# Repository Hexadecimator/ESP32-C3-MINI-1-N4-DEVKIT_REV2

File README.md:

# ESP32-C3-MINI-1-N4-DEVKIT_REV2
New and improved ESP32-C3-MINI-1-N4 Devkit

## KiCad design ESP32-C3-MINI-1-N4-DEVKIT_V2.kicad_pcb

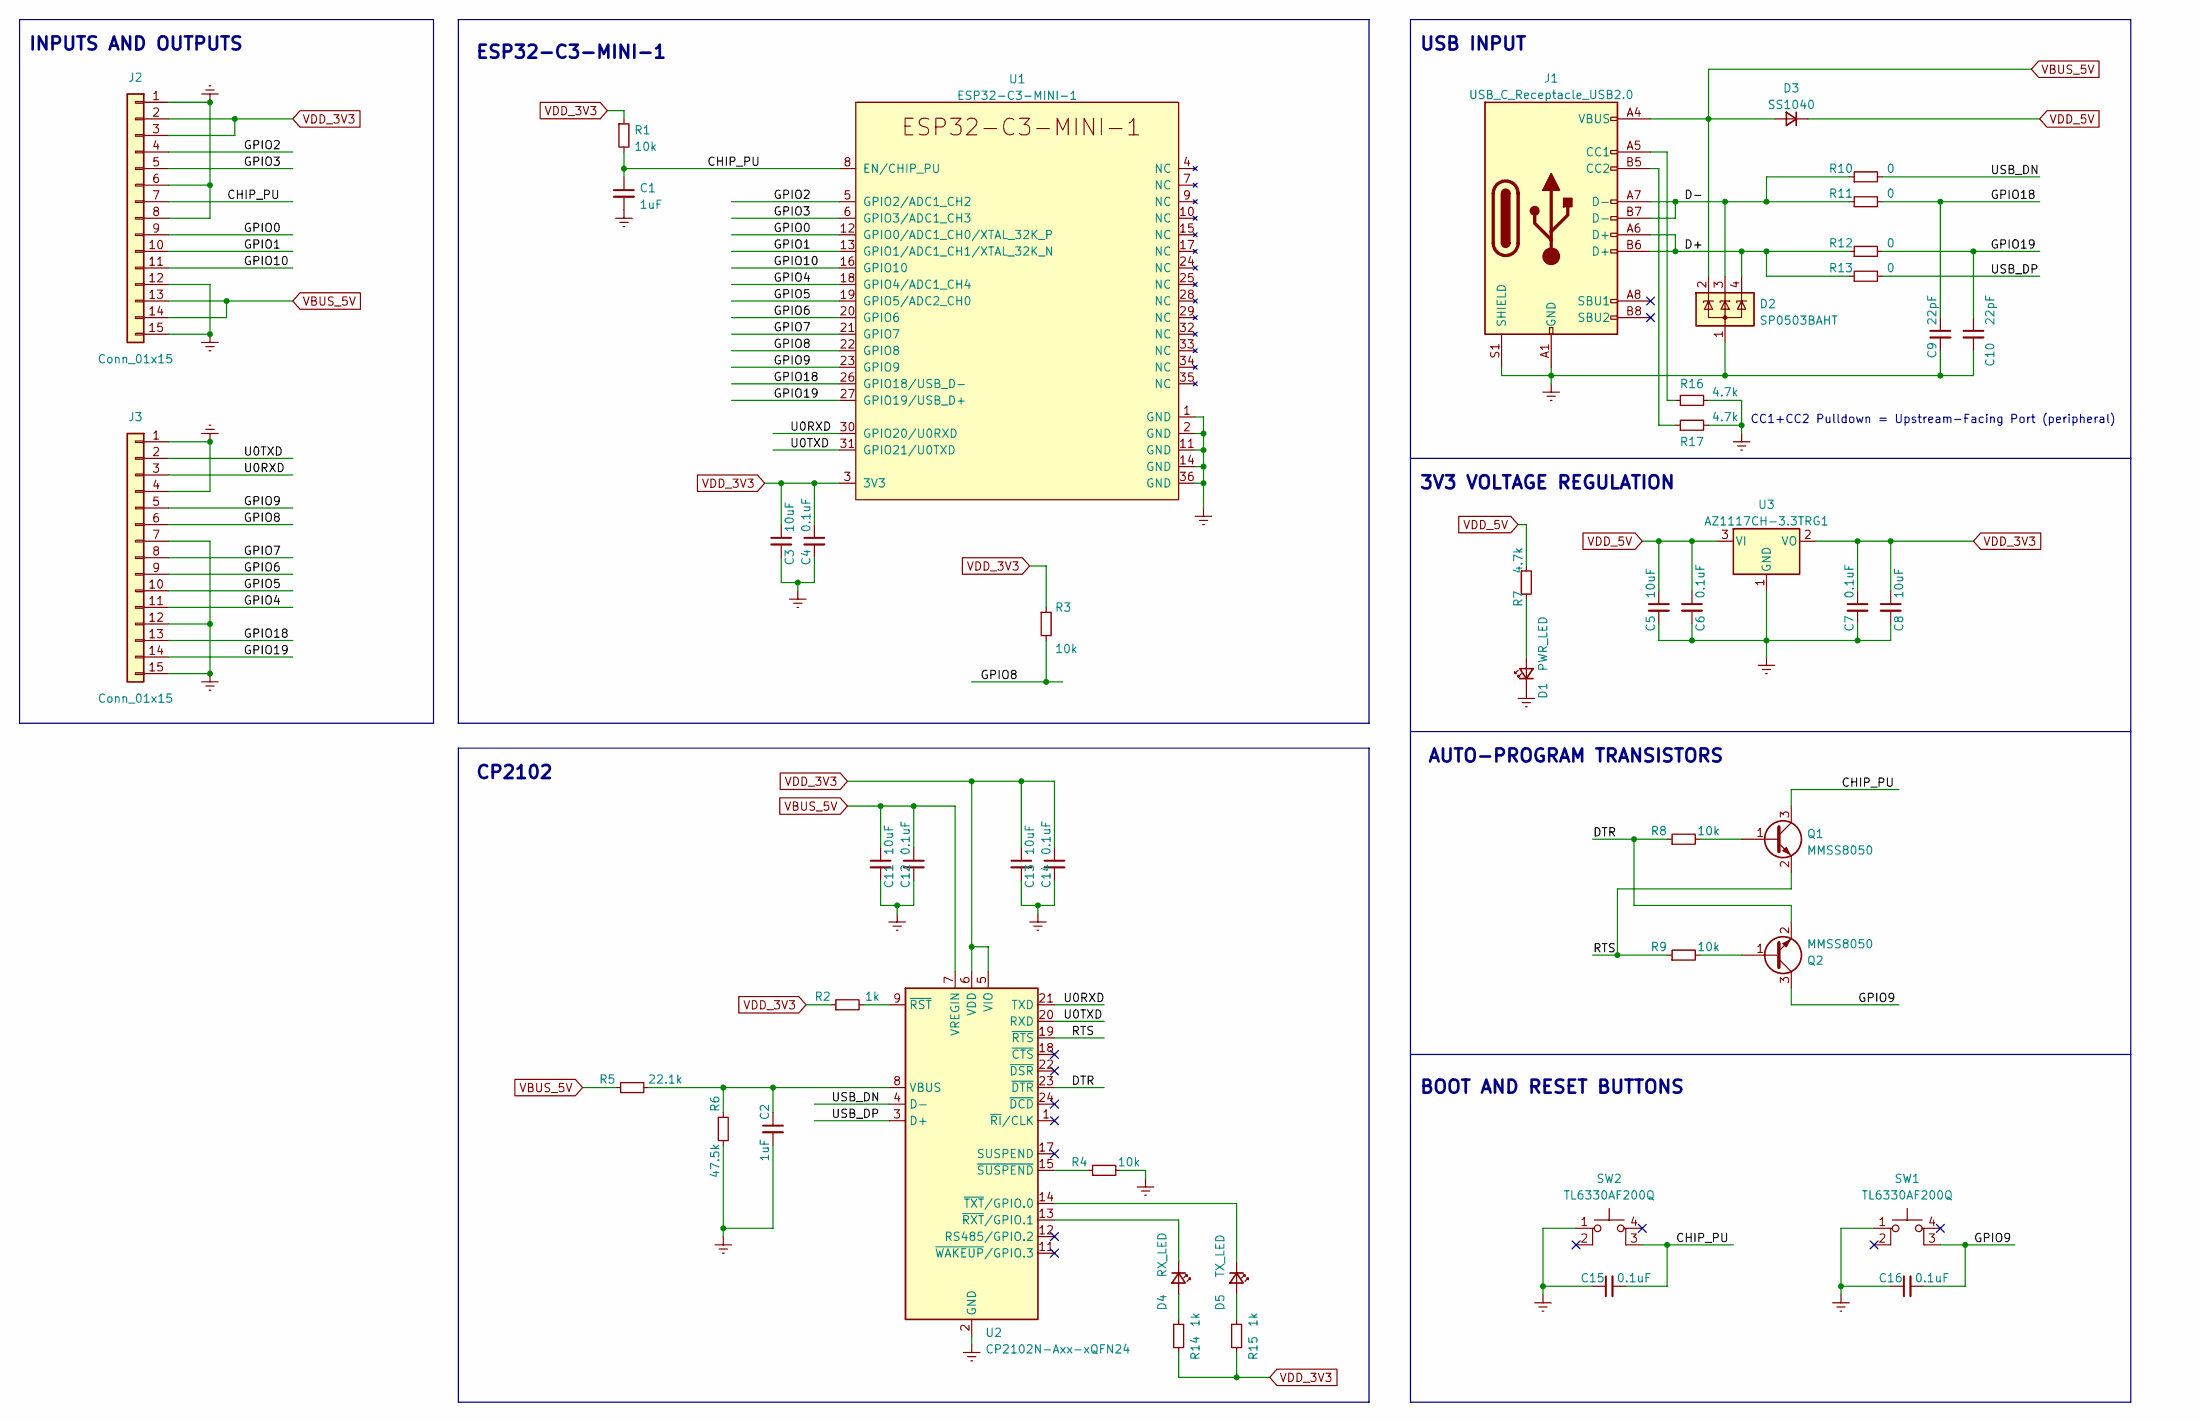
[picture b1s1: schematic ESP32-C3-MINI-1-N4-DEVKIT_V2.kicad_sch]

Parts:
C1, C2: 1uF; C_0603_1608Metric
C3, C5, C8, C11, C13: 10uF; C_0805_2012Metric
C4, C6, C7, C12, C14, C15, C16: 0.1uF; C_0603_1608Metric
C9, C10: 22pF; C_0603_1608Metric
D1: PWR_LED; D_0603_1608Metric
D2: SP0503BAHT; SOT-143
D3: SS1040; D_SOD-123
D4: RX_LED; D_0603_1608Metric
D5: TX_LED; D_0603_1608Metric
J1: USB_C_Receptacle_USB2.0; USB_C_Receptacle_HRO_TYPE-C-31-M-12
J2, J3: Conn_01x15; PinHeader_1x15_P2.54mm_Vertical
Q1, Q2: MMSS8050; SOT-23
R1, R3, R4, R8, R9: 10k; R_0603_1608Metric
R2, R14, R15: 1k; R_0603_1608Metric
R5: 22.1k; R_0603_1608Metric
R6: 47.5k; R_0603_1608Metric
R7, R16, R17: 4.7k; R_0603_1608Metric
R10, R11, R12, R13: 0; R_0603_1608Metric
SW1, SW2: TL6330AF200Q; SW_Push_1P1T_NO_CK_KMR2
U1: ESP32-C3-MINI-1
U2: CP2102N-Axx-xQFN24; QFN-24-1EP_4x4mm_P0.5mm_EP2.6x2.6mm
U3: AZ1117CH-3.3TRG1; SOT-223-3_TabPin2

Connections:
/CHIP_PU: C1.1, C15.2, J2.7, Q1.3 (C), R1.2, SW2.3 (K), U1.8 (EN/CHIP_PU)
/D+: D2.4 (K), J1.A6 (D+), J1.B6 (D+), R12.1, R13.1
/D-: D2.3 (K), J1.A7 (D-), J1.B7 (D-), R10.1, R11.1
/DTR: Q2.2 (E), R8.1, U2.23 (~DTR)
/GPIO0: J2.9, U1.12 (GPIO0/ADC1_CH0/XTAL_32K_P)
/GPIO1: J2.10, U1.13 (GPIO1/ADC1_CH1/XTAL_32K_N)
/GPIO2: J2.4, U1.5 (GPIO2/ADC1_CH2)
/GPIO3: J2.5, U1.6 (GPIO3/ADC1_CH3)
/GPIO4: J3.11, U1.18 (GPIO4/ADC1_CH4)
/GPIO5: J3.10, U1.19 (GPIO5/ADC2_CH0)
/GPIO6: J3.9, U1.20 (GPIO6)
/GPIO7: J3.8, U1.21 (GPIO7)
/GPIO8: J3.6, R3.2, U1.22 (GPIO8)
/GPIO9: C16.2, J3.5, Q2.3 (C), SW1.3 (K), U1.23 (GPIO9)
/GPIO10: J2.11, U1.16 (GPIO10)
/GPIO18: C9.1, J3.13, R11.2, U1.26 (GPIO18/USB_D-)
/GPIO19: C10.1, J3.14, R12.2, U1.27 (GPIO19/USB_D+)
/RTS: Q1.2 (E), R9.1, U2.19 (~RTS)
/U0RXD: J3.3, U1.30 (GPIO20/U0RXD), U2.21 (TXD)
/U0TXD: J3.2, U1.31 (GPIO21/U0TXD), U2.20 (RXD)
/USB_DN: R10.2, U2.4 (D-)
/USB_DP: R13.2, U2.3 (D+)
Earth: C1.2, C2.2, C3.2, C4.2, C5.2, C6.2, C7.2, C8.2, C9.2, C10.2, C11.2, C12.2, C13.2, C14.2, C15.1, C16.1, D1.1 (K), D2.1 (A), J1.A1 (GND), J1.A12 (GND), J1.B1 (GND), J1.B12 (GND), J1.S1 (SHIELD), J2.1, J2.6, J2.8, J2.12, J2.15, J3.1, J3.4, J3.7, J3.12, J3.15, R4.2, R6.2, R16.2, R17.2, SW1.1, SW2.1, U1.1 (GND), U1.2 (GND), U1.11 (GND), U1.14 (GND), U1.36 (GND), U2.2 (GND), U2.25 (GND), U3.1 (GND)
unnamed: D1.2 (A), R7.2
unnamed: D4.1 (K), U2.13 (~RXT/GPIO.1)
unnamed: D4.2 (A), R14.1
unnamed: D5.1 (K), U2.14 (~TXT/GPIO.0)
unnamed: D5.2 (A), R15.1
unnamed: J1.A5 (CC1), R16.1
unnamed: J1.B5 (CC2), R17.1
unnamed: Q1.1 (B), R8.2
unnamed: Q2.1 (B), R9.2
unnamed: R2.2, U2.9 (~RST)
unnamed: R4.1, U2.15 (~SUSPEND)
unnamed: C2.1, R5.2, R6.1, U2.8 (VBUS)
VBUS_5V: C11.1, C12.1, D2.2 (K), D3.2 (A), J1.A4 (VBUS), J1.A9 (VBUS), J1.B4 (VBUS), J1.B9 (VBUS), J2.13, J2.14, R5.1, U2.7 (VREGIN)
VDD_3V3: C3.1, C4.1, C7.1, C8.1, C13.1, C14.1, J2.2, J2.3, R1.1, R2.1, R3.1, R14.2, R15.2, U1.3 (3V3), U2.5 (VIO), U2.6 (VDD), U3.2 (VO)
VDD_5V: C5.1, C6.1, D3.1 (K), R7.1, U3.3 (VI)

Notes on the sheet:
ESP32-C3-MINI-1
3V3 VOLTAGE REGULATION
CC1+CC2 Pulldown = Upstream-Facing Port (peripheral)
USB INPUT
AUTO-PROGRAM TRANSISTORS
INPUTS AND OUTPUTS
CP2102
BOOT AND RESET BUTTONS

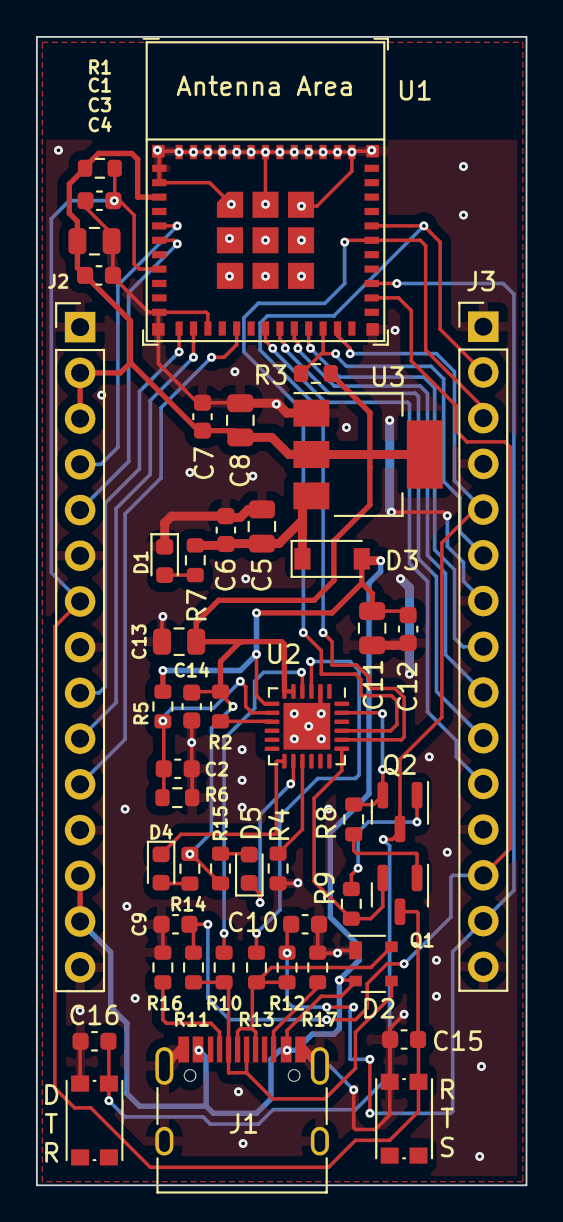
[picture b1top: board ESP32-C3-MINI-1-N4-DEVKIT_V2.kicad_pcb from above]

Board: 2 copper layers, 27.2 x 63.8 mm, 48 parts (0 on the bottom side), 38 nets.

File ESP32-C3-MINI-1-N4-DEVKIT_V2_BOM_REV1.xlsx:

Source:
Date: | 44788.761562500003
Tool: | Eeschema (6.0.5)
Generator:
Component Count: | 48
Individual Components:
Reference(s) | Value | LibPart | Footprint | Datasheet
C1 | 1uF | Device:C_Small | Capacitor_SMD:C_0603_1608Metric | ~
C2 | 1uF | Device:C_Small | Capacitor_SMD:C_0603_1608Metric | ~
C3 | 10uF | Device:C_Small | Capacitor_SMD:C_0805_2012Metric | ~
C4 | 0.1uF | Device:C_Small | Capacitor_SMD:C_0603_1608Metric | ~
C5 | 10uF | Device:C_Small | Capacitor_SMD:C_0805_2012Metric | ~
C6 | 0.1uF | Device:C_Small | Capacitor_SMD:C_0603_1608Metric | ~
C7 | 0.1uF | Device:C_Small | Capacitor_SMD:C_0603_1608Metric | ~
C8 | 10uF | Device:C_Small | Capacitor_SMD:C_0805_2012Metric | ~
C9 | 22pF | Device:C_Small | Capacitor_SMD:C_0603_1608Metric | ~
C10 | 22pF | Device:C_Small | Capacitor_SMD:C_0603_1608Metric | ~
C11 | 10uF | Device:C_Small | Capacitor_SMD:C_0805_2012Metric | ~
C12 | 0.1uF | Device:C_Small | Capacitor_SMD:C_0603_1608Metric | ~
C13 | 10uF | Device:C_Small | Capacitor_SMD:C_0805_2012Metric | ~
C14 | 0.1uF | Device:C_Small | Capacitor_SMD:C_0603_1608Metric | ~
C15 | 0.1uF | Device:C_Small | Capacitor_SMD:C_0603_1608Metric | ~
C16 | 0.1uF | Device:C_Small | Capacitor_SMD:C_0603_1608Metric | ~
D1 | PWR_LED | Device:LED_Small | Diode_SMD:D_0603_1608Metric | ~
D2 | SP0503BAHT | Power_Protection:SP0503BAHT | Package_TO_SOT_SMD:SOT-143 | http://www.littelfuse.com/~/media/files/littelfuse/technical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
D3 | SS1040 | Device:D_Small | Diode_SMD:D_SOD-123 | ~
D4 | RX_LED | Device:LED_Small | Diode_SMD:D_0603_1608Metric | ~
D5 | TX_LED | Device:LED_Small | Diode_SMD:D_0603_1608Metric | ~
J1 | USB_C_Receptacle_USB2.0 | Connector:USB_C_Receptacle_USB2.0 | Connector_USB:USB_C_Receptacle_HRO_TYPE-C-31-M-12 | https://www.usb.org/sites/default/files/documents/usb_type-c.zip
J2 | Conn_01x15 | Connector_Generic:Conn_01x15 | Connector_PinHeader_2.54mm:PinHeader_1x15_P2.54mm_Vertical | ~
J3 | Conn_01x15 | Connector_Generic:Conn_01x15 | Connector_PinHeader_2.54mm:PinHeader_1x15_P2.54mm_Vertical | ~
Q1 | MMSS8050 | Device:Q_NPN_BEC | Package_TO_SOT_SMD:SOT-23 | ~
Q2 | MMSS8050 | Device:Q_NPN_BEC | Package_TO_SOT_SMD:SOT-23 | ~
R1 | 10k | Device:R_Small | Resistor_SMD:R_0603_1608Metric | ~
R2 | 1k | Device:R_Small | Resistor_SMD:R_0603_1608Metric | ~
R3 | 10k | Device:R_Small | Resistor_SMD:R_0603_1608Metric | ~
R4 | 10k | Device:R_Small | Resistor_SMD:R_0603_1608Metric | ~
R5 | 22.1k | Device:R_Small | Resistor_SMD:R_0603_1608Metric | ~
R6 | 47.5k | Device:R_Small | Resistor_SMD:R_0603_1608Metric | ~
R7 | 4.7k | Device:R_Small | Resistor_SMD:R_0603_1608Metric | ~
R8 | 10k | Device:R_Small | Resistor_SMD:R_0603_1608Metric | ~
R9 | 10k | Device:R_Small | Resistor_SMD:R_0603_1608Metric | ~
R10 | 0 | Device:R_Small | Resistor_SMD:R_0603_1608Metric | ~
R11 | 0 | Device:R_Small | Resistor_SMD:R_0603_1608Metric | ~
R12 | 0 | Device:R_Small | Resistor_SMD:R_0603_1608Metric | ~
R13 | 0 | Device:R_Small | Resistor_SMD:R_0603_1608Metric | ~
R14 | 1k | Device:R_Small | Resistor_SMD:R_0603_1608Metric | ~
R15 | 1k | Device:R_Small | Resistor_SMD:R_0603_1608Metric | ~
R16 | 4.7k | Device:R_Small | Resistor_SMD:R_0603_1608Metric | ~
R17 | 4.7k | Device:R_Small | Resistor_SMD:R_0603_1608Metric | ~
SW1 | TL6330AF200Q | Switch:SW_MEC_5E | Button_Switch_SMD:SW_Push_1P1T_NO_CK_KMR2 | http://www.apem.com/int/index.php?controller=attachment&id_a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
SW2 | TL6330AF200Q | Switch:SW_MEC_5E | Button_Switch_SMD:SW_Push_1P1T_NO_CK_KMR2 | http://www.apem.com/int/index.php?controller=attachment&id_a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
U1 | ESP32-C3-MINI-1 | Espressif:ESP32-C3-MINI-1 | Espressif:ESP32-C3-MINI-1 | https://www.espressif.com/sites/default/files/documentation/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
U2 | CP2102N-Axx-xQFN24 | Interface_USB:CP2102N-Axx-xQFN24 | Package_DFN_QFN:QFN-24-1EP_4x4mm_P0.5mm_EP2.6x2.6mm | https://www.silabs.com/documents/public/data-sheets/cp2102n-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
U3 | AZ1117CH-3.3TRG1 | Regulator_Linear:AZ1117-3.3 | Package_TO_SOT_SMD:SOT-223-3_TabPin2 | https://www.diodes.com/assets/Datasheets/AZ1117.pdf
Collated Components:
Item | Qty | Reference(s) | Value | LibPart | Footprint | Datasheet
1 | 2 | C1, C2 | 1uF | Device:C_Small | Capacitor_SMD:C_0603_1608Metric | ~
2 | 5 | C3, C5, C8, C11, C13 | 10uF | Device:C_Small | Capacitor_SMD:C_0805_2012Metric | ~
3 | 7 | C4, C6, C7, C12, C14, C15, C16 | 0.1uF | Device:C_Small | Capacitor_SMD:C_0603_1608Metric | ~
4 | 2 | C9, C10 | 22pF | Device:C_Small | Capacitor_SMD:C_0603_1608Metric | ~
5 | 1 | D1 | PWR_LED | Device:LED_Small | Diode_SMD:D_0603_1608Metric | ~
6 | 1 | D2 | SP0503BAHT | Power_Protection:SP0503BAHT | Package_TO_SOT_SMD:SOT-143 | http://www.littelfuse.com/~/media/files/littelfuse/technical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
7 | 1 | D3 | SS1040 | Device:D_Small | Diode_SMD:D_SOD-123 | ~
8 | 1 | D4 | RX_LED | Device:LED_Small | Diode_SMD:D_0603_1608Metric | ~
9 | 1 | D5 | TX_LED | Device:LED_Small | Diode_SMD:D_0603_1608Metric | ~
10 | 1 | J1 | USB_C_Receptacle_USB2.0 | Connector:USB_C_Receptacle_USB2.0 | Connector_USB:USB_C_Receptacle_HRO_TYPE-C-31-M-12 | https://www.usb.org/sites/default/files/documents/usb_type-c.zip
11 | 2 | J2, J3 | Conn_01x15 | Connector_Generic:Conn_01x15 | Connector_PinHeader_2.54mm:PinHeader_1x15_P2.54mm_Vertical | ~
12 | 2 | Q1, Q2 | MMSS8050 | Device:Q_NPN_BEC | Package_TO_SOT_SMD:SOT-23 | ~
13 | 5 | R1, R3, R4, R8, R9 | 10k | Device:R_Small | Resistor_SMD:R_0603_1608Metric | ~
14 | 3 | R2, R14, R15 | 1k | Device:R_Small | Resistor_SMD:R_0603_1608Metric | ~
15 | 1 | R5 | 22.1k | Device:R_Small | Resistor_SMD:R_0603_1608Metric | ~
16 | 1 | R6 | 47.5k | Device:R_Small | Resistor_SMD:R_0603_1608Metric | ~
17 | 3 | R7, R16, R17 | 4.7k | Device:R_Small | Resistor_SMD:R_0603_1608Metric | ~
18 | 4 | R10, R11, R12, R13 | 0 | Device:R_Small | Resistor_SMD:R_0603_1608Metric | ~
19 | 2 | SW1, SW2 | TL6330AF200Q | Switch:SW_MEC_5E | Button_Switch_SMD:SW_Push_1P1T_NO_CK_KMR2 | http://www.apem.com/int/index.php?controller=attachment&id_a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
20 | 1 | U1 | ESP32-C3-MINI-1 | Espressif:ESP32-C3-MINI-1 | Espressif:ESP32-C3-MINI-1 | https://www.espressif.com/sites/default/files/documentation/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
21 | 1 | U2 | CP2102N-Axx-xQFN24 | Interface_USB:CP2102N-Axx-xQFN24 | Package_DFN_QFN:QFN-24-1EP_4x4mm_P0.5mm_EP2.6x2.6mm | https://www.silabs.com/documents/public/data-sheets/cp2102n-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
22 | 1 | U3 | AZ1117CH-3.3TRG1 | Regulator_Linear:AZ1117-3.3 | Package_TO_SOT_SMD:SOT-223-3_TabPin2 | https://www.diodes.com/assets/Datasheets/AZ1117.pdf

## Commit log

2022-08-03 most components placed
    most components are placed on the schematic and have their footprints assigned. Still need power (red) LED and RGB LED
2022-08-04 power and buttons done in schem
    todo: C3 mini + CP2102 the layout can begin
2022-08-05 wired cp2102, started C3 mini
2022-08-12 started layout
2022-08-12 layout has begun
2022-08-15 layout finished, still need silkscreen
2022-08-15 add image
2022-08-16 submitted to jlcpcb
2022-08-16 added bill of materials
2022-09-04 added build files for ease of access
2022-09-05 added pin 1 silkscreens
    added silkscreen dot for all parts with a required orientation (diodes and CP2102)
